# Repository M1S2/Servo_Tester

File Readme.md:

# Servo Tester

This is a simple servo tester PCB.

## PCB
The schematic and PCB are created using Fusion 360. It is designed to be manufactured using toner transfer method so all traces are as big as possible. This is only a one-sided PCB.

## Mechanic
There is no special housing for this servo tester.

The only mechanical parts are:
- USB_Plastic_Plate: a thin plastic plate to ensure the correct thickness of the USB-plug part. The complete thickness including the PCB, solder and the plastic plate should be approx. 2 mm.
- Potentiometer_Knob: a knob for easier operation of the potentiometer. This isn't necessary. The default potentiometer axis can also be used.

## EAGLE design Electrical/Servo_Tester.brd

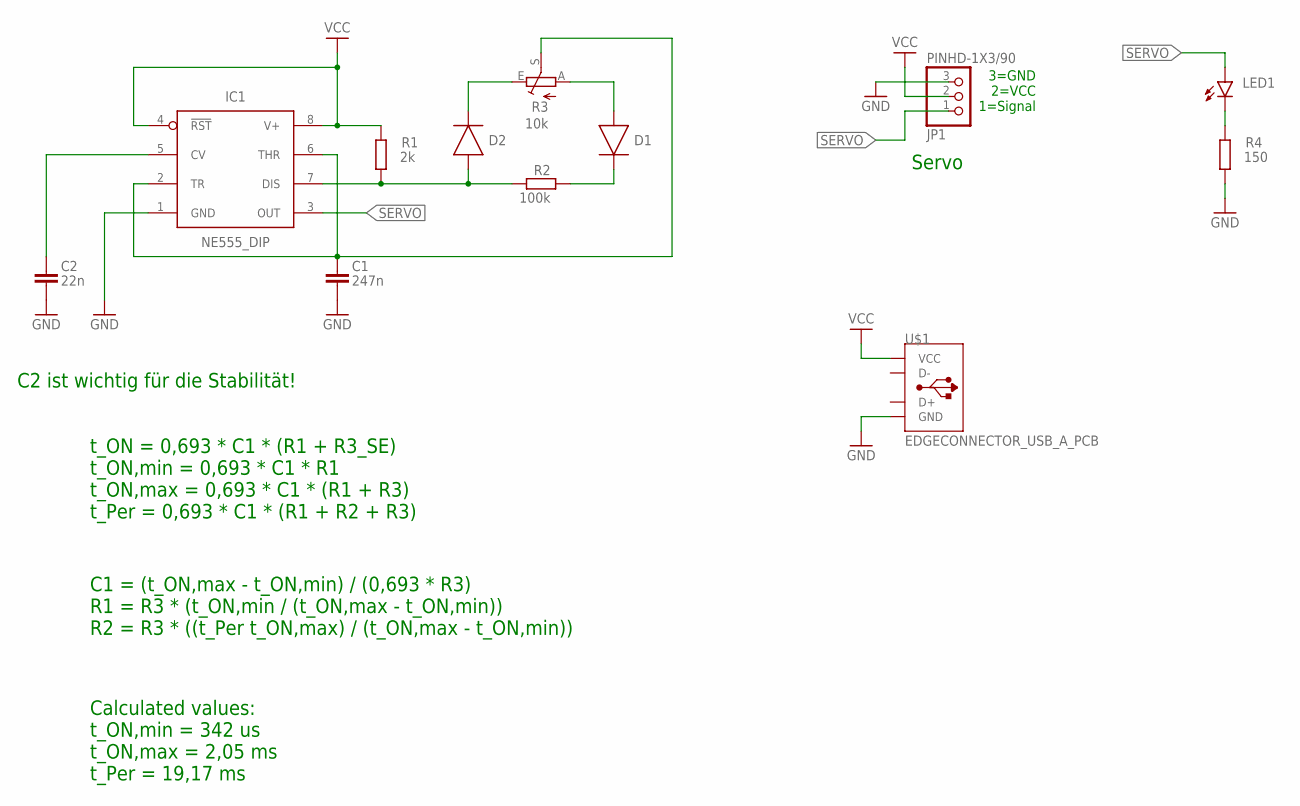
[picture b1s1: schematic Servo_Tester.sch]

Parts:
C1: 247n; CAPC2012X110
C2: 22n; CAPC2012X110
D1, D2: DIODE_LL4148_SOD-80; DIOMELF3516
IC1: NE555_DIP; DIP826W53P254L959H508Q8B
JP1: PINHD-1X3/90; 1X03/90
LED1: LEDCHIP-LED0805; CHIP-LED0805
R1: 2k; R0805
R2: 100k; R0805
R3: 10k; LI15
R4: 150; R0805
U$1: EDGECONNECTOR_USB_A_PCB

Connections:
GND: C1.2, C2.2, IC1.1 (GND), JP1.3, R4.1, U$1.GND
unnamed: C2.1, IC1.5 (CV)
unnamed: C1.1, IC1.2 (TR), IC1.6 (THR), R3.S
unnamed: D2.2 (A), IC1.7 (DIS), R1.1, R2.1
unnamed: D1.1 (C), R2.2
unnamed: D2.1 (C), R3.E
unnamed: D1.2 (A), R3.A
unnamed: LED1.C, R4.2
SERVO: IC1.3 (OUT), JP1.1, LED1.A
VCC: IC1.4 (!RST), IC1.8 (V+), JP1.2, R1.2, U$1.VCC

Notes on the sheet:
C2 ist wichtig für die Stabilität!
3=GND 2=VCC 1=Signal
Servo
t_ON = 0,693 * C1 * (R1 + R3_SE) t_ON,min = 0,693 * C1 * R1 t_ON,max = 0,693 * C1 * (R1 + R3) t_Per = 0,693 * C1 * (R1 + R2 + R3)
C1 = (t_ON,max - t_ON,min) / (0,693 * R3) R1 = R3 * (t_ON,min / (t_ON,max - t_ON,min)) R2 = R3 * ((t_Per t_ON,max) / (t_ON,max - t_ON,min))
Calculated values: t_ON,min = 342 us t_ON,max = 2,05 ms t_Per = 19,17 ms

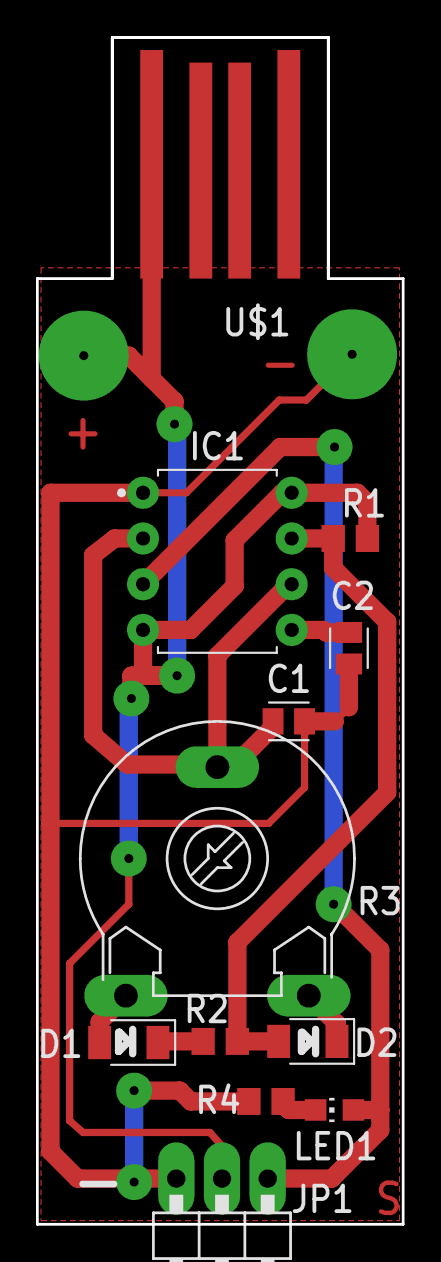
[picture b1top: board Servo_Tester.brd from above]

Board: 2 copper layers, 20.3 x 65.9 mm, 12 parts (0 on the bottom side), 10 nets.

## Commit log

2023-11-04 Initial version tracked by GIT (milestone V1.0) in Fusion360
2023-11-04 Added LED to PCB, slightly adapted some texts
